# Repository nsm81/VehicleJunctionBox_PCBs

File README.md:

# VehicleJunctionBox
The junction box is an intermediate stage between the accumulator and inverter. It contains an HVD, a current sensor, discharge circuitry, TSAL and TSMPs. 

## PCBs & Enclosure

## Block Diagram

## Current Sense MCU IO
| Description  | IO |
| ------------- | ------------- |
| Local Fault | IO34 |
| Upstream Fault | IO35 |
| STATUS LED | IO12 |
| CAN RX | IO32 |
| CAN TX | IO26 |
| SDA | IO4 |
| SCL | IO15 |
| VREF | IO19 |
| LEM_OUT | IO21 |

## DTM PinOut
| Pin  | Description |
| ------------- | ------------- |
| 1 | GLV+ |
| 2 | BSPD Test Current + |
| 3 | BSPD Test Current - |
| 4 | GND |
| 5 | DOC Fault |
| 6 | TSAL Green |
| 7 | TSAL Red |
| 8 | BSPD 5kW Detect |
| 9 | CAN+ |
| 10 | CAN- |
| 11 | SD Loop In |
| 12 | SD Loop Out |

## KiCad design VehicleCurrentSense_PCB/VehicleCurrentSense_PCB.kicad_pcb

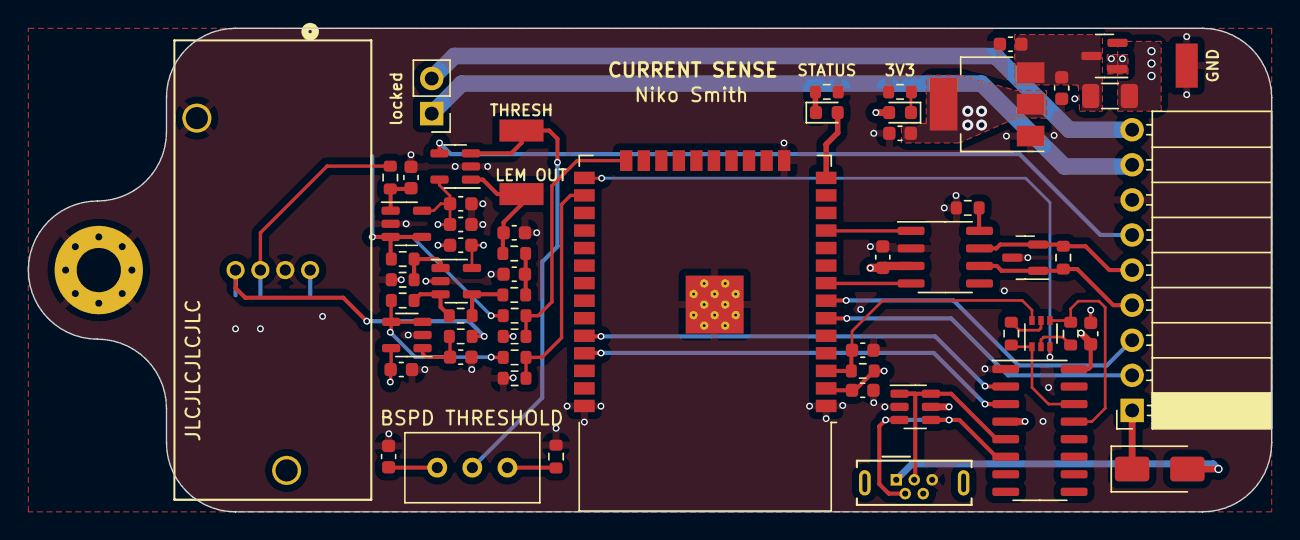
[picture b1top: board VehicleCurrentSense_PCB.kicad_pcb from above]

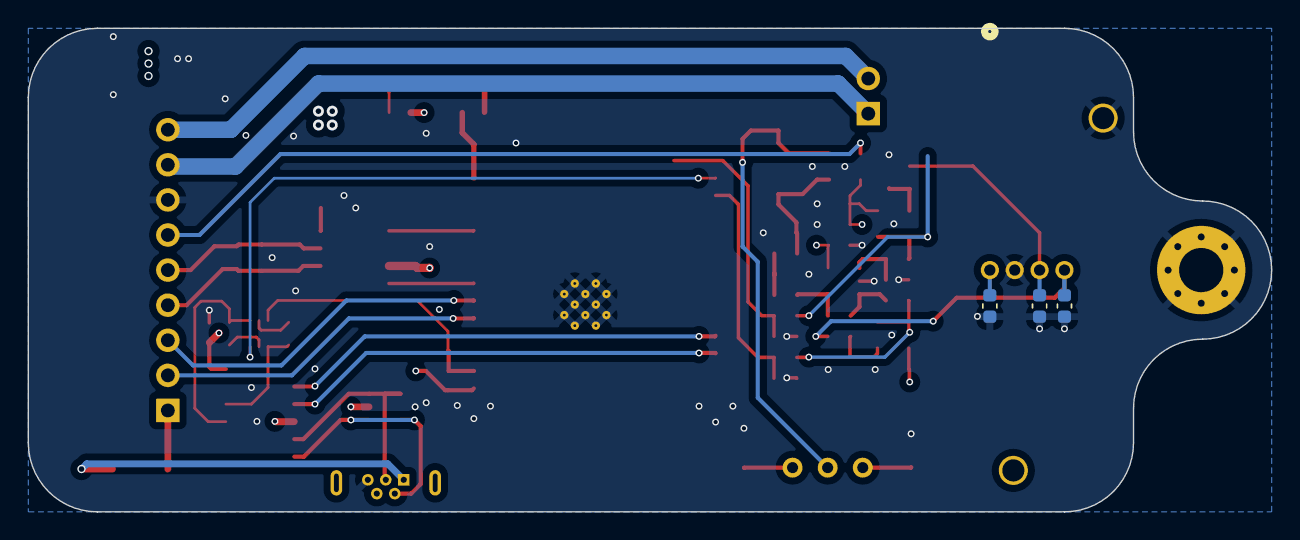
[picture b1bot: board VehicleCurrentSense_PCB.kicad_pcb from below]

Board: 4 copper layers, 90.0 x 35.0 mm, 64 parts (3 on the bottom side), 43 nets.

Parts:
C1, C3: 47n; C_0603_1608Metric
C2: 4.7n; C_0603_1608Metric
C4, C5: 1u; C_0603_1608Metric
C6, C8, C10, C11, C12, C16, C19, C20: 100n; C_0603_1608Metric
C7, C15: 22u; C_0603_1608Metric
C13: 0.1uF; C_0603_1608Metric
C14, C17, C18: 10u; C_0603_1608Metric
D1: 771-PLVA650A; SOT-23
D2: SS34; D_SMA
D3: GREEN; LED_0603_1608Metric
D4: SM712_SOT23; SOT-23
D5: Green; LED_0603_1608Metric
F1: 1A; Fuse_1206_3216Metric
H2: MountingHole_Pad; MountingHole_3.2mm_M3_Pad_Via
J1: Conn_01x07; PinSocket_1x09_P2.54mm_Horizontal
J3: Test Current; PinHeader_1x02_P2.54mm_Vertical
J4: USB_B_Micro; USB_Micro-B_Wuerth_614105150721_Vertical
Q1: BC847BS; SOT-363_SC-70-6
R1, R2: 3.3k; R_0603_1608Metric
R9: 2.2k; R_0603_1608Metric
R10, R11, R12, R13, R17, R18, R19, R20: 10k; R_0603_1608Metric
R14: 120; R_0603_1608Metric
R21: 4.2k; R_0603_1608Metric
R22, R23: 2k; R_0603_1608Metric
R24, R25, R28: 100k; R_0603_1608Metric
R26, R27: 1.6k; R_0603_1608Metric
RV2: 100k; Potentiometer_Bourns_3296W_Vertical
TP1: GND; 1206 Testpoint
TP3: Vdiff; 1206 Testpoint
TP4: Thresh; 1206 Testpoint
U1: HAIS 100-P; HAIS_P_LEM
U2, U6, U10: LMV321; SOT-23-5
U3: AMS1117-3.3; SOT-223-3_TabPin2
U5: USBLC6-2SC6; SOT-23-6
U7: ESP32-WROOM-32
U8: CH340C; SOIC-16_3.9x9.9mm_P1.27mm
U9: SN65HVD230; SOIC-8_3.9x4.9mm_P1.27mm
U11: TL331; SOT-23-5

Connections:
3V3 LEM_OUT: R17.2, R18.1, U7.24 (IO2)
3V3 VREF: R19.2, R20.1, U7.26 (IO4)
+3V3: C11.2, C12.2, C13.2, C15.1, D5.2 (A), R10.2, U3.2 (VO), U7.2 (VDD), U8.4 (V3), U8.16 (VCC), U9.3 (VCC)
+5V: C3.1, C6.1, C8.1, C16.1, C19.1, C20.1, D2.1 (K), F1.1, J1.1, RV2.3, U1.1 (+5V), U2.5 (V+), U5.5 (VBUS), U6.5 (V+), U10.5 (V+), U11.5 (V+)
BSPD: J1.6, U11.4
BSPD Test Current +: J1.8, J3.1
BSPD Test Current -: J1.9, J3.2
BSPD Threshold: RV2.2, TP4.1, U11.3 (+)
CAN+: D4.2 (A2), J1.5, R14.2, U9.7 (CANH)
CAN-: D4.1 (A1), J1.4, R14.1, U9.6 (CANL)
CAN_RX: U7.8 (IO32), U9.4 (R)
CAN_TX: U7.11 (IO26), U9.1 (D)
D+: J4.3 (D+), U5.1 (I/O1), U5.6 (I/O1), U8.5 (UD+)
D-: J4.2 (D-), U5.3 (I/O2), U5.4 (I/O2), U8.6 (UD-)
DTR: Q1.4 (E2), R12.2, U8.13 (~DTR)
EN: C10.1, Q1.6 (C1), R10.1, U7.3 (EN)
GND: C1.2, C2.2, C3.2, C4.2, C5.2, C6.2, C7.2, C8.2, C10.2, C11.1, C12.1, C13.1, C14.2, C15.2, C16.2, C17.2, C18.2, C19.2, C20.2, D1.1 (A), D4.3 (common), H2.1, J1.7, J4.5 (GND), R9.1, R11.2, R18.2, R20.2, R21.1, R24.2, R28.2, TP1.1, U1.2 (GND), U1.5 (CORE), U2.2 (V-), U3.1 (GND), U5.2 (GND), U6.2 (V-), U7.1 (GND), U7.15 (GND), U7.38 (GND), U7.39 (GND), U8.1 (GND), U9.2 (GND), U10.2 (V-), U11.2 (V-)
IO0: Q1.3 (C2), U7.25 (IO0)
LEM_OUT: R17.1, R23.2, U6.3 (-), U6.4
Local: J1.3, U7.7 (IO35)
unnamed: C17.1, R26.2, R27.1
unnamed: C7.1, C14.1, D1.3 (K), F1.2, U3.3 (VI)
unnamed: D2.2 (A), J4.1 (VBUS)
unnamed: D3.1 (K), R9.2
unnamed: D5.1 (K), R21.2
unnamed: Q1.2 (B1), R12.1
unnamed: Q1.5 (B2), R13.1
unnamed: R25.1, R26.1, U10.4
unnamed: R28.1, RV2.1
unnamed: C2.1, R1.1, U1.3 (OUTPUT)
unnamed: C4.1, R2.2, U2.1 (+)
unnamed: C5.1, R1.2, U6.1 (+)
unnamed: R11.1, U9.8 (Rs)
unnamed: R23.1, R24.1, U10.1 (+)
unnamed: R22.1, R25.2, U10.3 (-)
unnamed: C18.1, R27.2, TP3.1, U11.1 (-)
RTS: Q1.1 (E1), R13.2, U8.14 (~RTS)
RxD: U7.35 (TXD0/IO1), U8.3 (RXD)
Status_LED: D3.2 (A), U7.14 (IO12)
TxD: U7.34 (RXD0/IO3), U8.2 (TXD)
Upstream: J1.2, U7.6 (IO34)
VREF: C1.1, R2.1, U1.4 (VREF)
VREF_OUT: R19.1, R22.2, U2.3 (-), U2.4

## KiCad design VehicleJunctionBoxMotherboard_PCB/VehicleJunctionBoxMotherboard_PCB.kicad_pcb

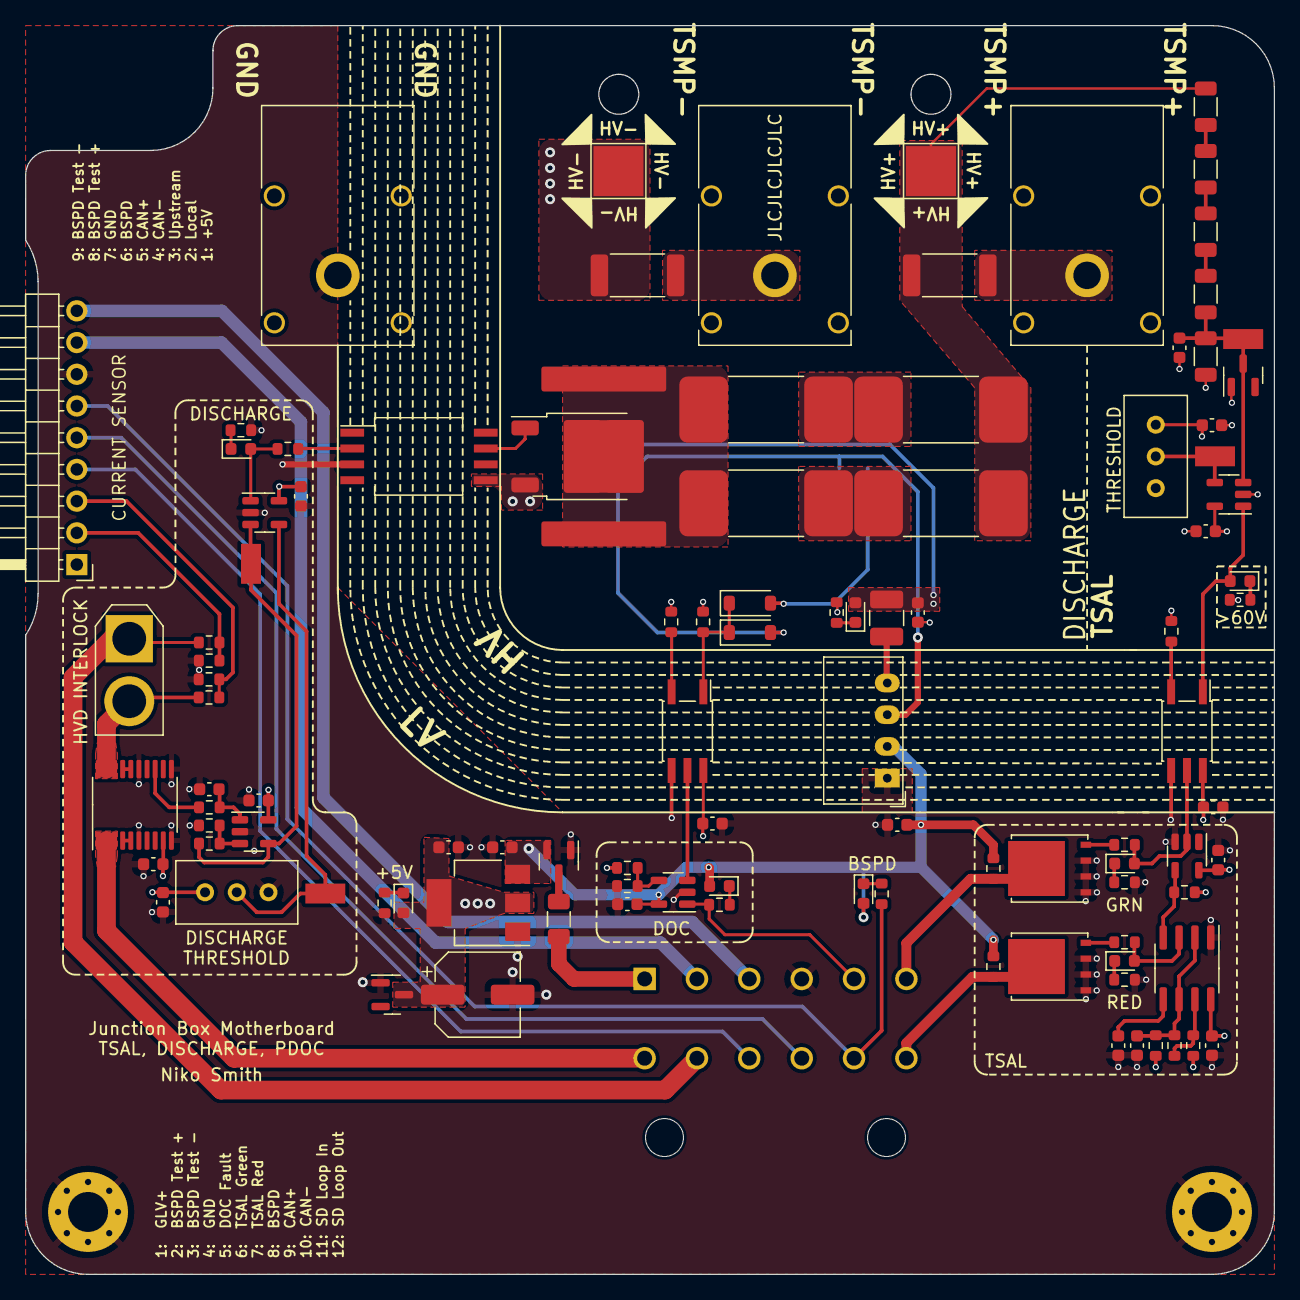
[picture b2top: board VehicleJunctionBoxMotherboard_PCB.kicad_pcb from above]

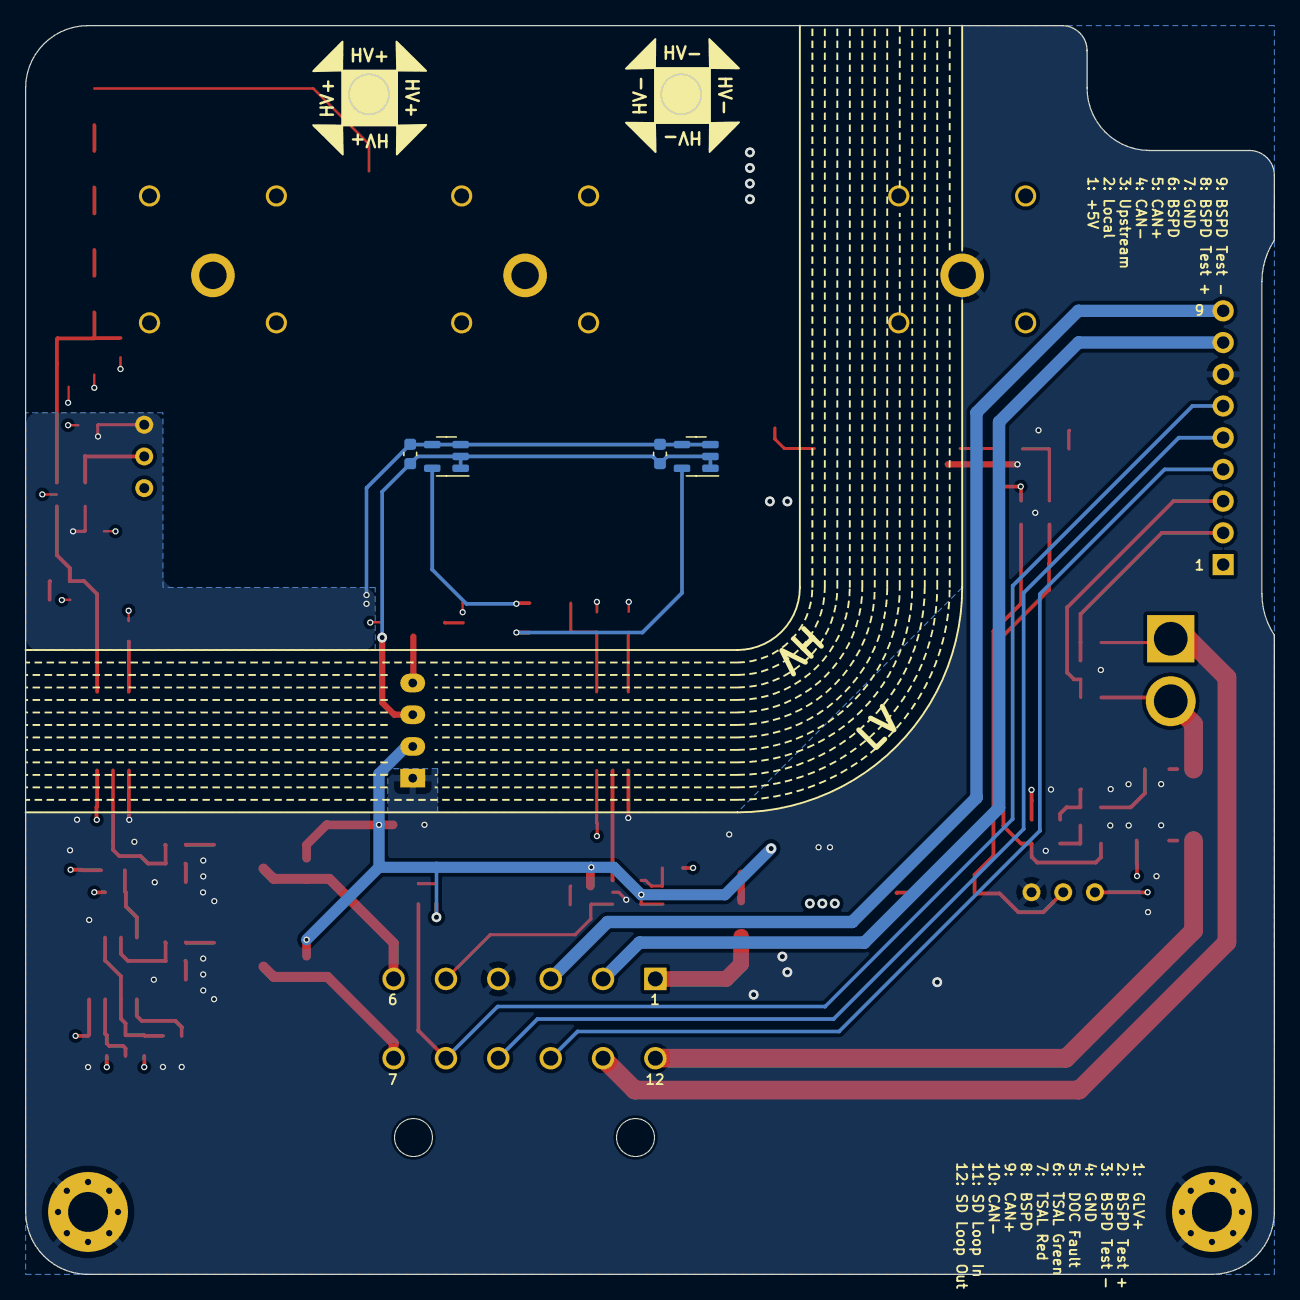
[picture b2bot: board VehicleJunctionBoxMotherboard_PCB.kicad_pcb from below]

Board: 4 copper layers, 100.0 x 100.0 mm, 111 parts (4 on the bottom side), 66 nets.

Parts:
C1, C2: 22u; C_0603_1608Metric
C3: 330n; C_0603_1608Metric
C4, C5, C6, C10, C11, C12, C13, C14, C16, C18, C19, C20, C23, C25, C26: 100n; C_0603_1608Metric
C7: 4.7u; C_0603_1608Metric
C8: 100u; CP_Elec_6.3x5.4
C15: 10n; C_0603_1608Metric
C17: 10u; C_0603_1608Metric
D1, D2, D4, D5, D6, D7, D12: Green; LED_0603_1608Metric
D3, D11: 771-PLVA650A; SOT-23
D8, D10: 1N4148W; D_SOD-123
D9: Red; LED_0603_1608Metric
F2: 2A; Fuse_1206_3216Metric
H3, H4: MountingHole_Pad; MountingHole_3.2mm_M3_Pad_Via
HS1: Heatsink_Pad_2Pin; MOSFET Heatsink
J1: HVD IL; AMASS_XT30U-F_1x02_P5.0mm_Vertical
J2: Vehicle; TE_DTM13-12PA
J3: TSMP+; Banana_Cliff_FCR7350x_S16N-PC_Horizontal
J4: TSMP-; Banana_Cliff_FCR7350x_S16N-PC_Horizontal
J5: HV+; TestPoint_Pad_4.0x4.0mm
J6: HV-; TestPoint_Pad_4.0x4.0mm
J7: TSMP GLV-; Banana_Cliff_FCR7350x_S16N-PC_Horizontal
J9: Conn_01x07; PinHeader_1x09_P2.54mm_Horizontal
L1: 47u; L_1210_3225Metric_Pad1.42x2.65mm_HandSolder
Q1: IXTY1R6N100D2; TO-252-2
Q3, Q4: FDMS86255; TDSON-8-1
Q5: SSM3J328R LF; SOT-23
R1, R2, R3, R4: DIS-10k; R_4020_10251Metric
R5, R19, R24: 4.7k; R_0603_1608Metric
R6, R9: 15k; R_2512_6332Metric_Pad1.40x3.35mm_HandSolder
R7, R10, R17, R31: 4.2k; R_0603_1608Metric
R8, R11, R20, R23, R33, R49: 10k; R_0603_1608Metric
R12, R13, R14, R15: 510k; R_1206_3216Metric
R16: 25k; R_1206_3216Metric
R18, R30, R35, R37: 1k; R_0603_1608Metric
R21: 1M; R_0603_1608Metric
R22: 16k; R_0603_1608Metric
R25, R26: 100R; R_0603_1608Metric
R27, R28: 100k; R_0603_1608Metric
R29: 11k; R_0603_1608Metric
R32: 330R; R_0603_1608Metric
R39, R43: 5.6k; R_0603_1608Metric
R41, R42: 18k; R_0603_1608Metric
RV1, RV2: 100k; Potentiometer_Bourns_3296W_Vertical
TP1: TS Voltage Divider; 1206 Testpoint
TP2: ISense Out; 1206 Testpoint
TP3, TP4: Thresh; 1206 Testpoint
U1: AMS1117-5.0; SOT-223-3_TabPin2
U2, U6, U10: TLV7031DBV; SOT-23-5
U3, U5: MCP9502PT-115E; SOT-23-5
U4: CRE1S1205SC; Converter_DCDC_Murata_CRE1xxxxxxSC_THT
U7, U20: TLP2361; SO-5_4.4x3.6mm_P1.27mm
U8: SN74LVC1G04DBVT; SOT-23-5
U9: NA555D; SOIC-8_3.9x4.9mm_P1.27mm
U12: INA253; TSSOP-20_4.4x6.5mm_P0.65mm
U13: LMV321; SOT-23-5
U15: ACPL-K30T-000E; SSO-8_6.8x5.9mm_P1.27mm_Clearance8mm

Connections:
+5V: C2.1, C5.2, C8.1, C13.1, C14.1, C16.1, C18.1, C19.1, C20.2, C25.1, D1.2 (A), D11.3 (K), J9.1, R11.1, R20.2, R21.1, R22.1, RV2.3, U1.2 (VO), U7.6 (VDD), U8.5, U9.8 (VCC), U10.5 (V+), U12.9 (VS), U13.5 (V+), U20.6 (VDD)
+5VA: C7.1, C11.1, C12.1, C23.2, C26.2, D2.2 (A), L1.2, RV1.3, U2.5 (V+), U3.3 (Hyst), U3.4 (VDD), U5.3 (Hyst), U5.4 (VDD)
BSPD: J2.8, J9.6, R5.1
BSPD Test Current +: J2.2, J9.8
BSPD Test Current -: J2.3, J9.9
CAN+: J2.9, J9.5
CAN-: J2.10, J9.4
DISCHARGE_THRESHOLD: RV2.2, TP3.1, U10.4 (-)
DOC_FLT: J2.5, R35.1, U6.1
DOC_Thresh: R11.2, R33.1, U6.4 (-)
GLV+: C1.1, C4.2, C6.1, D6.2 (A), D12.2 (A), Q5.2 (S), R27.1, R28.1, U1.3 (VI), U4.2 (+VIN), U6.5 (V+)
GND: C1.2, C2.2, C3.2, C4.1, C5.1, C6.2, C8.2, C13.2, C14.2, C15.2, C16.2, C17.2, C18.2, C19.2, C20.1, C25.2, D11.1 (A), H3.1, H4.1, J2.4, J7.1, J9.7, Q3.1 (S), Q3.2 (S), Q3.3 (S), Q4.1 (S), Q4.2 (S), Q4.3 (S), Q5.1 (G), R7.1, R19.2, R24.2, R30.1, R31.1, R33.2, R39.2, R43.2, RV2.1, U1.1 (GND), U4.1 (-VIN), U6.2 (V-), U7.4 (GND), U8.3, U9.1 (GND), U10.2 (V-), U12.6 (GND), U12.10 (REF2), U12.11 (REF1), U12.15 (GND), U13.2 (V-), U15.3, U20.4 (GND)
HV+: J5.1, R3.2, R4.2, R6.1, R12.2
HV-: C7.2, C10.2, C11.2, C12.2, C23.1, C26.1, D3.1 (A), J6.1, Q1.3 (S), R9.1, R10.1, R16.1, R17.1, R18.1, R37.1, R49.1, RV1.1, U2.2 (V-), U3.1 (GND), U3.2 (GND), U4.3 (-VOUT), U5.1 (GND), U5.2 (GND), U15.5
Local: J9.3, R41.2, R43.1
unnamed: D1.1 (K), R7.2
unnamed: D2.1 (K), R10.2
unnamed: C10.1, D3.3 (K), R15.1, R16.2, TP1.1, U2.3 (+)
unnamed: D4.2 (A), U2.1, U7.1 (A)
unnamed: D4.1 (K), R17.2
unnamed: D5.2 (A), R32.2, U10.1
unnamed: D5.1 (K), R31.2
unnamed: D6.1 (K), R35.2
unnamed: D7.2 (A), R25.1, U7.5 (VO), U8.2
unnamed: D7.1 (K), R19.1
unnamed: D8.2 (A), U5.5 (Out)
unnamed: D9.2 (A), R26.1, U9.3 (Q)
unnamed: D9.1 (K), R24.1
unnamed: D10.2 (A), U3.5 (Out)
unnamed: D8.1 (K), D10.1 (K), R49.2, U20.1 (A)
unnamed: D12.1 (K), R5.2
unnamed: F2.1, J2.1
unnamed: J3.1, R6.2
unnamed: J4.1, R9.2
unnamed: HS1.1, HS1.2, Q1.2 (D), R1.1, R2.1
unnamed: Q1.1 (G), U15.7
unnamed: Q3.4 (G), R25.2
unnamed: Q4.4 (G), R26.2
unnamed: F2.2, Q5.3 (D)
unnamed: R1.2, R3.1
unnamed: R2.2, R4.1
unnamed: R12.1, R13.2
unnamed: R13.1, R14.2
unnamed: R14.1, R15.2
unnamed: R32.1, U15.2
unnamed: L1.1, U4.4 (+VOUT)
unnamed: R18.2, U7.3 (K)
unnamed: C15.1, U9.5 (CV)
unnamed: R22.2, R23.1, U9.7 (DIS)
unnamed: C17.1, R21.2, R23.2, U9.2 (TR), U9.6 (THR)
unnamed: R29.1, TP2.1, U10.3 (+), U13.4
unnamed: U12.16 (IN+), U12.17 (SH+)
unnamed: U12.4 (SH-), U12.5 (IN-)
unnamed: R8.1, U12.13 (OUT)
unnamed: C3.1, R8.2, U13.1 (+)
unnamed: R29.2, R30.2, U13.3 (-)
unnamed: R37.2, U20.3 (K)
unnamed: U6.3 (+), U20.5 (VO)
RESET: R20.1, U8.4, U9.4 (R)
SD_LP_FROM_HVD: J1.2, R41.1, U12.18 (IS+), U12.19 (IS+), U12.20 (IS+)
SD_LP_IN: J1.1, J2.11, R42.1
SD_LP_OUT: J2.12, U12.1 (IS-), U12.2 (IS-), U12.3 (IS-)
TS Detection Threshold: RV1.2, TP4.1, U2.4 (-)
TSAL_GRN: J2.6, Q3.5 (D), R27.2
TSAL_RED: J2.7, Q4.5 (D), R28.2
Upstream: J9.2, R39.1, R42.2

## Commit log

2023-06-27 Submitted for Manufacturing
2023-08-02 Optimised
